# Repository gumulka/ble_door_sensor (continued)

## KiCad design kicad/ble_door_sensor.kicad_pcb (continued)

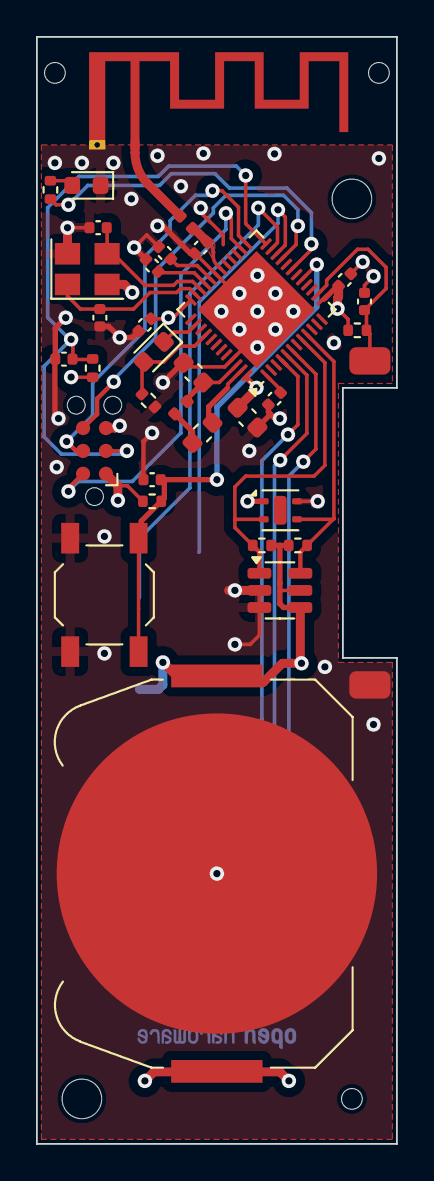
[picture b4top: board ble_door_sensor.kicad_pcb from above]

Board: 4 copper layers, 20.0 x 61.5 mm, 40 parts (1 on the bottom side), 29 nets.

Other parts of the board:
H201, H202: MountingHole; MountingHole_2.2mm_M2

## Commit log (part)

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2023-12-01 Initial commit send out to production
2024-02-10 Add battery voltage to measurement data
    measure the SOC voltage and calculate a battery percentage from it
    Not good, but better then nothing
2024-02-10 Optimizing power consmption
    reducing BLE adv schedule to only once per 10 seconds
    Disabling UART by default.
2024-02-10 First reading out of the hall sensors
    Only printing out a message on change.
2024-02-10 Add BTHome support
    Transmitting the sensor values via BTHome advertisement data
2024-02-10 Add Zephyr project structure
    Moved hardware files to new subdirectory called kicad.
2024-02-14 Add reference datasheets
2024-02-14 Add footprint for reed sensor
2024-02-14 Ignoring fp-info-chache
    It should have been ignored from the beginning, but I was an idiot
2024-02-14 Updated schematic
2024-02-14 First rough placement
    Updated some footprints in the process to better fit my needs
    Holes are in 5mm grid to each other 15mm in x and 45 mm in y apart
    Board outline is 20x80mm
2024-02-14 First routing
    Replaced Testpoints with SMD pinheader
    Added more Testpoints
    Reduced board outline to 20x70mm
    Mounting holes are now 15x35mm apart
2024-02-14 Add datasheet for processor
2024-02-14 Put the reed contact on the top side
    I want to glue the PCB to some surfaces and having something on the
    bottom side is very contraproductive.
2024-02-16 Add Temperature sensor instead of external reed
    Remove the contacts fro external reed contacts
    Add temperature sensor
    Reduce the size of the PCB
    Add additional mounting hole
2024-02-23 Add tmp100 sensor for temperature
    also added mounting holes for assembly machines
2024-02-26 Add ambient light and humidity sensor
2024-02-29 Add MPN and Manufacturer for most parts
    To be able to order from different houses
2024-03-19 Update to Kicad 8
2024-03-20 Add 3D-Model of humidity sensor
2024-03-20 Move footprints to new library
2024-03-20 Move generate_output into library
2024-05-04 Update zephyr devicetree to new revision
    I don't plan on using the first revision ever again, therefor there is
    no need to preserve the devicetree for the old revision.
2024-05-04 Add support Temperature/Humidity sensor
    First support for reading out values from the dual sensor.
2024-05-07 Add support for update over the air
    Using MCUBOOT as a bootloader and partition the device into A/B
    schema to have a somewhat save update.
    During updateting, the device often did halt, so instead of halting the
    system I overwrote the error handler to reboot instead, making it
    possible to restart the update without having to manually restarting
    the device.
2024-05-07 Add Phototransistor
    Add support for the phototransistor to measure ambient light.
    Needed to change the name to fit all data into ble advertisement.
2024-05-11 Fix high current consumption
    There is a hardware bug on the SOC that I'm using, which has to have
    a workaround when using i2c and gpiote at the same time, which i do.
2024-05-11 Move environment sensor measurements out of main
    to have a better overview of the sensors and where the data gets
    collected, I started to separate the main file into multiple.
2024-05-11 Move interrupt sensors into its own file
    Interrupts may be able to reschedule the reading of sensors and
    trigger with it a reading of themself.
2024-05-11 Differentiate between short and long button press
2024-05-11 Move battery measurement scale
    Old was from 2.5 to 3.3V
    New is 2.0 to 3.0, which is much more realistic for 2032 batteries
2024-05-11 Remove power management from light sensor
2024-05-12 final touches
    Some final touches to make it an overall nicer output
2024-05-30 Add datasheet for humidity sensor
2024-05-30 Added hints about i"c addresses
2024-05-30 Added hints about i2c addresses
2024-05-30 Ad case for device.
    Case designed in FreeCAD and needs some more love, but good enough
    for a first draft.
2025-03-09 Show status of hal sensor on first boot
    indicating with the LED if the hal-sensor is closed or not, to help
    user add the magnet to the device during install.
    This stops after pressing the button once and is restored by a
    powercycle.
2025-03-09 Basic measurements
2025-03-25 Update to newest zephyr version
    Changed board definition to fit the newest version needs
2025-03-25 light sensor: make use of runtime power management
    Using runtime power management yields better and more general results
    for power savings.
2025-03-26 Make every environment sensor optional
    Every Sensor is not optional and can be omitted in the devicetree.
    that currently makes the code a lot more cluttered, but it is a step
    towards a better organization.
2025-06-26 Update to kicad 9
2025-06-26 Move all sensors to their own sheet
2025-07-20 Move sensors to a new different sheet
2025-07-20 Add NXP W71 Board based on NINA-B506 from u-blox
2025-07-20 Add STM32WB55 based board
2025-07-26 kicad: minimal: add minimal PCB design
    To test with devboards if nothing else is available.
